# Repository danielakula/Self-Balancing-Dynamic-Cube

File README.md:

# Self-Balancing-Dynamic-Cube
Cubli inspired project for 3rd year undergraduate dissertation. Objective is to achieve balance on three edges, corner, and jump from face to edge.

# Contents
ESP32_Tests is written code for each tests done on the firmware.

Edge Balance is the code that implements an inner LQR control loop and a PI outer loop to achieve edge balance on Motor1.

UI Balance is a test which adds wireless UI onto Edge Balance.

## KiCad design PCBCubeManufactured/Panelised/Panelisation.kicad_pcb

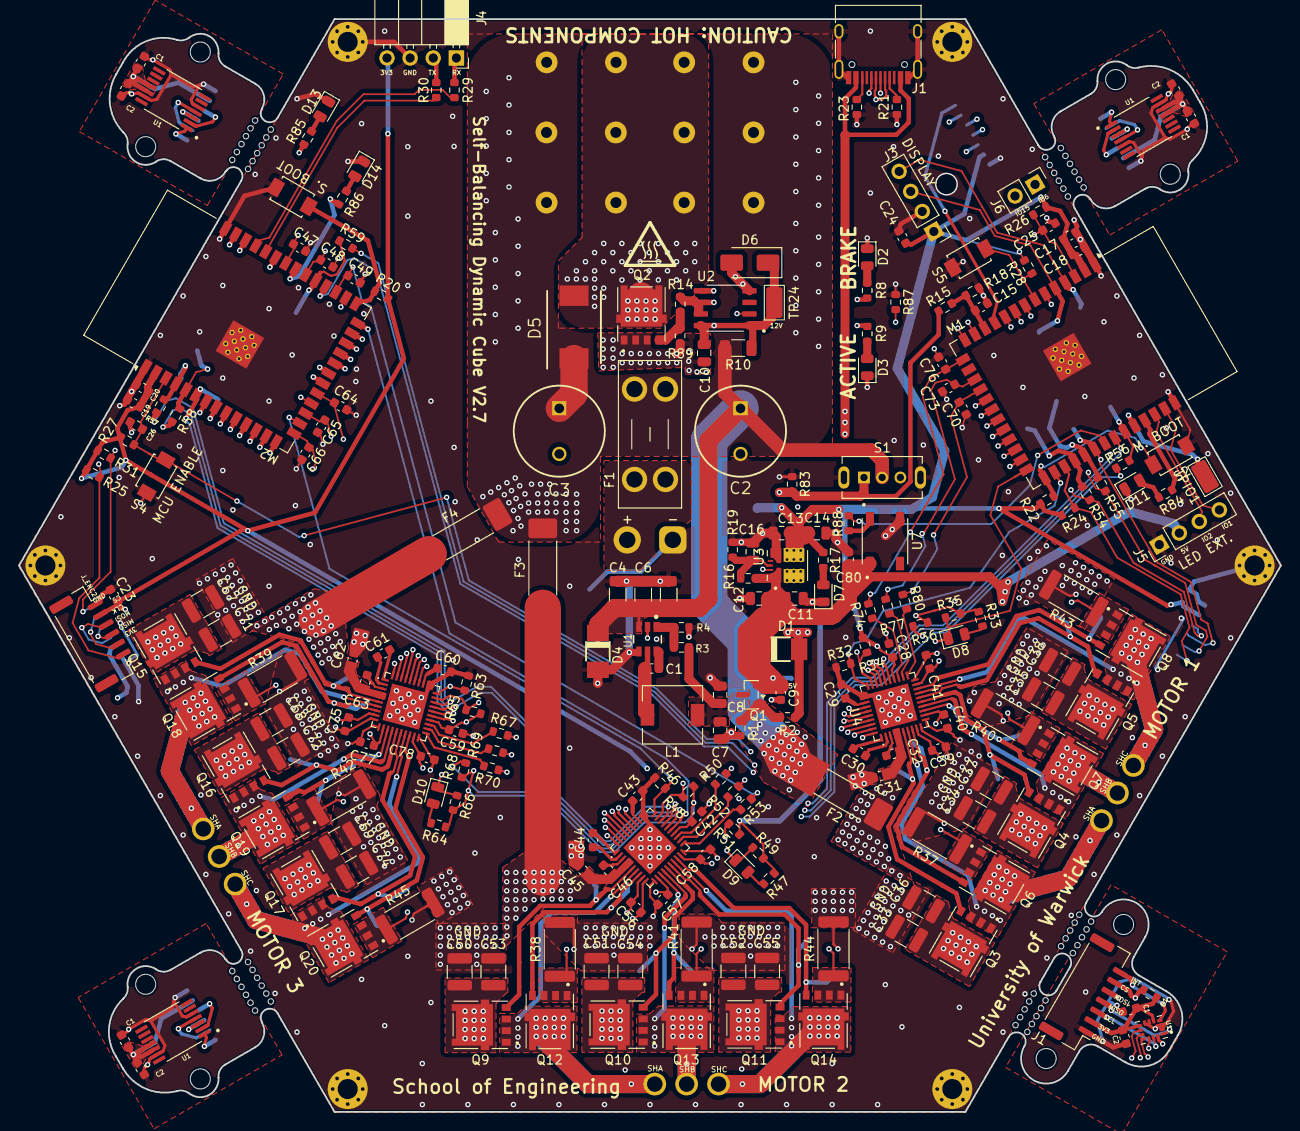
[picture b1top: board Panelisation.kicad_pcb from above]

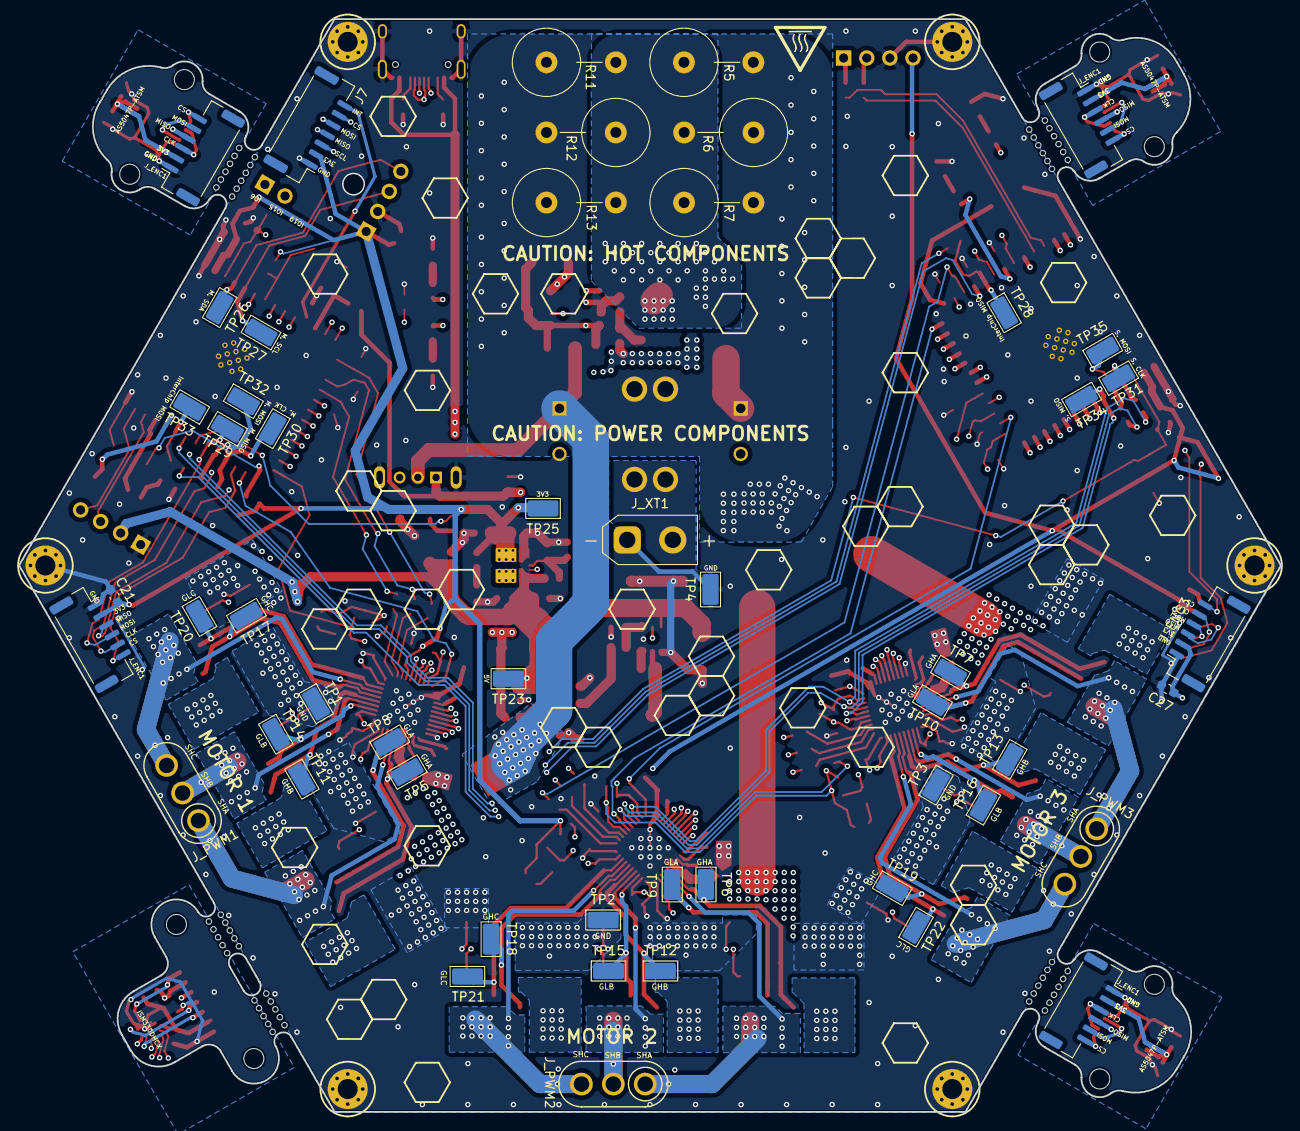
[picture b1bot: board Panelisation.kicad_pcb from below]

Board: 4 copper layers, 138.6 x 120.0 mm, 291 parts (53 on the bottom side), 181 nets.

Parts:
C1, C1#2, C1#3, C1#4, C1#5, C2#2, C15, C18, C20, C21, C23, C24, C27, C28, C31, C42, C45, C59, C62, C80: 100nF; C_0603_1608Metric
C2, C3: EEU-FC1H471L; CAPPRD500W85D1000H3200
C2#3, C2#4, C2#5, C9, C17, C19: 10uF; C_0603_1608Metric
C4, C5: 4.7uF; C_1206_3216Metric
C6: 100nF; C_1206_3216Metric
C7, C8: 47uF; C_0805_2012Metric
C10, C11, C16: 10uF; C_0805_2012Metric
C12: 100nF; C_0805_2012Metric
C13, C14: 22uF; C_0805_2012Metric
C25, C26, C29, C32, C43, C46, C60, C63: 1uF; C_0603_1608Metric
C30, C44, C61: 47nF; C_0603_1608Metric
C33, C34, C35, C36, C37, C38, C50, C51, C52, C53, C54, C55, C67, C68, C69, C71, C72, C74: 10uF; C_1210_3225Metric
C39, C40, C41, C56, C57, C58, C75, C77, C78: 1000pF; C_0603_1608Metric
C47, C48, C49, C64, C65, C66, C70, C73, C76: 2.2nF; C_0603_1608Metric
D1, D4: D_Schottky SS34; DO-214AC
D2, D8, D9, D10, D11, D14: LED R; LED_0805_2012Metric
D3, D7, D13: LED G; LED_0805_2012Metric
D5: D_Schottky SS1045; DIOM8059X256N
D6: 12V Zener; D_SMA
F1: 3568; Fuseholder_Blade_Mini_Keystone_3568
F2, F3, F4: 0456020.ER; FUSC10030X305N
H1, H2, H3, H4, H5, H6: MountingHole_Pad; MountingHole_2.19mm_M2_Pad_Via
J1, J7: Conn_01x07; JST_GH_BM07B-GHS-TBT_1x07-1MP_P1.25mm_Vertical
J1#2: USB_C_Receptacle_USB2.0_16P; USB_C_Receptacle_HRO_TYPE-C-31-M-12
J3, J5: Conn_01x04; PinHeader_1x04_P2.54mm_Vertical
J4: Conn_01x04; PinSocket_1x04_P2.54mm_Horizontal
J6: Conn_01x02; PinHeader_1x02_P2.54mm_Vertical
J_ENC1, J_ENC1#2, J_ENC1#3, J_ENC1#4, J_ENC2, J_ENC3: Conn_01x06; JST_GH_SM06B-GHS-TB_1x06-1MP_P1.25mm_Horizontal
J_PWM1, J_PWM2, J_PWM3: Conn_01x03; Amass_MR30PB-M
J_XT1: XT30UPB-M; AMASS_XT30UPB-M_1x02_P5.0mm_Vertical
L1: 4.7uH; L_6.3x6.3_H3
LOGO3, LOGO3#2: CAUTION HOT SURFACE; IEC_HotSurface_Small
M1, M2: ESP32-S3-WROOM-1
NT1, NT2, NT3, NT4, NT5, NT6, NT7, NT8, NT9, NT10: NetTie_2; NET-TIE-0.25mm
Q1: AO3401A; SOT-23
Q2, Q3, Q4, Q5, Q6, Q7, Q8, Q9, Q10, Q11, Q12, Q13, Q14, Q15, Q16, Q17, Q18, Q19, Q20: NTMFS5C612N; NTMFS5C430NT1G
R1, R1#2, R18, R19, R20, R22, R26, R27, R28, R87, R89: 10k; R_0603_1608Metric
R2: 1k; R_0603_1608Metric
R3, R15, R83: 100k; R_0603_1608Metric
R4: 19.1k; R_0603_1608Metric
R5, R6, R7, R11, R12, R13: AC07000003308JAC00; AC05
R8, R9: 2.2k; R_0603_1608Metric
R10: 330; R_1206_3216Metric
R14: 10; R_0603_1608Metric
R16: 15.8k; R_0603_1608Metric
R17: 470; R_0603_1608Metric
R21, R23: 5.1k; R_0603_1608Metric
R24, R25, R31, R32, R34, R35, R36, R46, R48, R49, R51, R63, R65, R66, R68: 10K; R_0603_1608Metric
R29, R30, R84, R85, R86, R88: 330; R_0603_1608Metric
R33, R47, R64: 1.5k; R_0603_1608Metric
R37, R38, R39, R40, R41, R42, R43, R44, R45: Shunt; R_2512_6332Metric
R50, R52, R53, R67, R69, R70, R74, R77, R80: 56; R_0603_1608Metric
R54, R55, R56, R57, R58, R59: 33; R_0603_1608Metric
S1: SS12D07VG4; SW_SS12D07VG4
S2, S3, S4, S5: TS-1088-AR02016; SW_TS-1088-AR02016
TP1, TP2, TP3, TP4, TP5, TP6, TP7, TP8, TP9, TP10, TP11, TP12, TP13, TP14, TP15, TP16, TP17, TP18, TP19, TP20, TP21, TP22, TP23, TP24, TP25, TP26, TP27, TP28, TP29, TP30, TP31, TP32, TP33, TP34, TP35: TestPoint; TestPoint_Keystone_5015_Micro_Mini
TPIO1: TestPoint; TestPoint_Keystone_5015_Micro_Mini
U1, U1#3, U1#5: AS5047P-ATSM; SOP65P640X120-14N
U1#2: LMR51625YFDDCR; DDC0006A-MFG
U1#4: ISM330DHCX; PQFN50P250X300X86-14N
U2: MCP1407-E_SN
U3: TPSM863253RDXR; VREG_TPSM863253RDXR
U4, U5, U6: DRV8323SRTAT; DRV8323SRTAT_update_solder
U7: WS2812B-B; LED_WS2812B-B

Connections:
+3V3: C1.1, C1#2.1, C1#4.1, C1#5.1, C2#2.1, C2#3.1, C2#4.1, C2#5.1, C13.2, C14.2, C17.2, C18.2, C19.2, C20.2, C21.2, C23.2, C24.2, C27.2, C28.2, C42.2, C59.2, J1.2, J3.1, J4.4, J7.2, J_ENC1.2, J_ENC1#2.2, J_ENC1#3.2, J_ENC1#4.2, J_ENC2.2, J_ENC3.2, M1.2 (3V3), M2.2 (3V3), R1#2.2, R17.2, R20.1, R22.1, R24.2, R25.2, R26.1, R27.1, R28.1, R31.2, R33.1, R34.2, R35.2, R36.2, R47.1, R48.2, R49.2, R51.2, R64.1, R65.2, R66.2, R68.2, TP25.1, U1.11 (VDD), U1.12 (VDD3V3), U1#3.11 (VDD), U1#3.12 (VDD3V3), U1#4.5 (VDD_IO), U1#4.8 (VDD), U1#5.11 (VDD), U1#5.12 (VDD3V3), U3.3 (VOUT), U3.7 (FB), U4.24 (VREF), U5.24 (VREF), U6.24 (VREF)
+5V: C9.2, C11.2, C12.2, C80.2, D1.1 (K), J5.2, Q1.2 (S), R16.1, TP23.1, U3.1 (VIN), U7.1 (VDD)
+5V Buck: C7.2, C8.2, L1.2, Q1.3 (D), R3.1
+5V USB: D1.2 (A), J1#2.A4 (VBUS), J1#2.A9 (VBUS), J1#2.B4 (VBUS), J1#2.B9 (VBUS), R2.1
/AO3401A Gate: Q1.1 (G), R1.1, R2.2
/BR3_EN: C16.2, R16.2, R19.2, U3.6 (EN)
/BR5_CB: C1#3.2, U1#2.6 (CB)
/BR5_FB: R3.2, R4.2, U1#2.1 (FB)
/BR5_SW: C1#3.1, L1.1, U1#2.5 (SW)
/BR_LEDG: D3.2 (A), R9.1
/BR_LEDR: D2.2 (A), R8.1
/CC1: J1#2.A5 (CC1), R21.2
/CC2: J1#2.B5 (CC2), R23.1
/CLK: J_ENC1.3, J_ENC1#3.3, J_ENC1#4.3, U1.2 (CLK), U1#3.2 (CLK), U1#5.2 (CLK)
/CS: J_ENC1.6, J_ENC1#3.6, J_ENC1#4.6, U1.1 (CSN), U1#3.1 (CSN), U1#5.1 (CSN)
/DIN: R88.2, U7.4 (DIN)
/Drain_Brake: D5.2 (A), Q2.5 (D), R5.1, R6.2, R7.1, R11.2, R12.1, R13.2
/Driver1/CPH1: C30.1, U4.2 (CPH)
/Driver1/CPL1: C30.2, U4.1 (CPL)
/Driver1/DVDD: C29.2, U4.33 (DVDD)
/Driver1/GHA: Q3.4 (G), TP5.1, U4.6 (GHA)
/Driver1/GHB: Q4.4 (G), TP11.1, U4.15 (GHB)
/Driver1/GHC: Q5.4 (G), TP17.1, U4.16 (GHC)
/Driver1/GLA: Q6.4 (G), TP8.1, U4.8 (GLA)
/Driver1/GLB: Q7.4 (G), TP14.1, U4.13 (GLB)
/Driver1/GLC: Q8.4 (G), TP20.1, U4.18 (GLC)
/Driver1/LED R1: D8.2 (A), R33.2
/Driver1/PhaseA: J_PWM1.1, Q3.1 (S), Q6.5 (D), U4.7 (SHA)
/Driver1/PhaseB: J_PWM1.2, Q4.1 (S), Q7.5 (D), U4.14 (SHB)
/Driver1/PhaseC: J_PWM1.3, Q5.1 (S), Q8.5 (D), U4.17 (SHC)
/Driver1/SNA: C39.1, NT4.2, U4.10 (SNA)
/Driver1/SNB: C40.1, NT2.2, U4.11 (SNB)
/Driver1/SNC: C41.1, NT3.2, U4.20 (SNC)
/Driver1/SPA: C39.2, Q6.1 (S), R37.1, U4.9 (SPA)
/Driver1/SPB: C40.2, Q7.1 (S), R40.1, U4.12 (SPB)
/Driver1/SPC: C41.2, Q8.1 (S), R43.1, U4.19 (SPC)
/Driver1/VCP1: C32.2, U4.3 (VCP)
/Driver1/VFuse: C31.2, C32.1, C33.2, C34.2, C35.2, C36.2, C37.2, C38.2, F2.1, Q3.5 (D), Q4.5 (D), Q5.5 (D), U4.4 (VM), U4.5 (VDRAIN)
/Driver2/CPH1: C44.1, U5.2 (CPH)
/Driver2/CPL1: C44.2, U5.1 (CPL)
/Driver2/DVDD: C43.2, U5.33 (DVDD)
/Driver2/GHA: Q9.4 (G), TP6.1, U5.6 (GHA)
/Driver2/GHB: Q10.4 (G), TP12.1, U5.15 (GHB)
/Driver2/GHC: Q11.4 (G), TP18.1, U5.16 (GHC)
/Driver2/GLA: Q12.4 (G), TP9.1, U5.8 (GLA)
/Driver2/GLB: Q13.4 (G), TP15.1, U5.13 (GLB)
/Driver2/GLC: Q14.4 (G), TP21.1, U5.18 (GLC)
/Driver2/LED R1: D9.2 (A), R47.2
/Driver2/PhaseA: J_PWM2.1, Q9.1 (S), Q12.5 (D), U5.7 (SHA)
/Driver2/PhaseB: J_PWM2.2, Q10.1 (S), Q13.5 (D), U5.14 (SHB)
/Driver2/PhaseC: J_PWM2.3, Q11.1 (S), Q14.5 (D), U5.17 (SHC)
/Driver2/SNA: C56.1, NT7.2, U5.10 (SNA)
/Driver2/SNB: C57.1, NT5.2, U5.11 (SNB)
/Driver2/SNC: C58.1, NT6.2, U5.20 (SNC)
/Driver2/SPA: C56.2, Q12.1 (S), R38.1, U5.9 (SPA)
/Driver2/SPB: C57.2, Q13.1 (S), R41.1, U5.12 (SPB)
/Driver2/SPC: C58.2, Q14.1 (S), R44.1, U5.19 (SPC)
/Driver2/VCP1: C46.2, U5.3 (VCP)
/Driver2/VFuse: C45.2, C46.1, C50.2, C51.2, C52.2, C53.2, C54.2, C55.2, F3.1, Q9.5 (D), Q10.5 (D), Q11.5 (D), U5.4 (VM), U5.5 (VDRAIN)
/Driver3/CPH1: C61.1, U6.2 (CPH)
/Driver3/CPL1: C61.2, U6.1 (CPL)
/Driver3/DVDD: C60.2, U6.33 (DVDD)
/Driver3/GHA: Q15.4 (G), TP7.1, U6.6 (GHA)
/Driver3/GHB: Q16.4 (G), TP13.1, U6.15 (GHB)
/Driver3/GHC: Q17.4 (G), TP19.1, U6.16 (GHC)
/Driver3/GLA: Q18.4 (G), TP10.1, U6.8 (GLA)
/Driver3/GLB: Q19.4 (G), TP16.1, U6.13 (GLB)
/Driver3/GLC: Q20.4 (G), TP22.1, U6.18 (GLC)
/Driver3/LED R1: D10.2 (A), R64.2
/Driver3/PhaseA: J_PWM3.1, Q15.1 (S), Q18.5 (D), U6.7 (SHA)
/Driver3/PhaseB: J_PWM3.2, Q16.1 (S), Q19.5 (D), U6.14 (SHB)
/Driver3/PhaseC: J_PWM3.3, Q17.1 (S), Q20.5 (D), U6.17 (SHC)
/Driver3/SNA: C75.1, NT10.2, U6.10 (SNA)
/Driver3/SNB: C77.1, NT8.2, U6.11 (SNB)
/Driver3/SNC: C78.1, NT9.2, U6.20 (SNC)
/Driver3/SPA: C75.2, Q18.1 (S), R39.1, U6.9 (SPA)
/Driver3/SPB: C77.2, Q19.1 (S), R42.1, U6.12 (SPB)
/Driver3/SPC: C78.2, Q20.1 (S), R45.1, U6.19 (SPC)
/Driver3/VCP1: C63.2, U6.3 (VCP)
/Driver3/VFuse: C62.2, C63.1, C67.2, C68.2, C69.2, C71.2, C72.2, C74.2, F4.1, Q15.5 (D), Q16.5 (D), Q17.5 (D), U6.4 (VM), U6.5 (VDRAIN)
/Gate_Brake: Q2.4 (G), R14.1, R89.1
/I.C. MISO: M2.31 (IO38), R59.1, TP28.1
/I.C. MOSI: M1.35 (IO42), R56.1, TP33.1
/LEDG: D7.2 (A), R17.1
/M. CLK: M1.30 (IO37), R54.1, TP30.1
/M. LEDR: D11.2 (A), R84.2
/M. MOSI: M1.31 (IO38), R55.1, TP32.1
/MISO: J_ENC1.4, J_ENC1#3.4, J_ENC1#4.4, U1.3 (MISO), U1#3.3 (MISO), U1#5.3 (MISO)
/MOSI: J_ENC1.5, J_ENC1#3.5, J_ENC1#4.5, U1.4 (MOSI), U1#3.4 (MOSI), U1#5.4 (MOSI)
/Out: R8.2, R14.2, U2.6 (OUT), U2.7 (OUT)
/S. CLK: M2.4 (IO4), R57.2, TP31.1
/S. LEDG: D13.2 (A), R85.2
/S. LEDR: D14.2 (A), R86.2
/S. MOSI: M2.5 (IO5), R58.2, TP35.1
/SRX: J4.1, R30.1
/STX: J4.2, R29.1
/V_XT30: F1.1, J_XT1.2 (+)
Debug1: J6.1, M1.6 (IO6)
Debug2: J6.2, M1.8 (IO15)
Display Button: M1.7 (IO7), R28.2, S5.2
Enable1: M1.28 (IO35), R32.2, U4.30 (ENABLE)
Enable2: M2.16 (IO46), R46.2, U5.30 (ENABLE)
Enable3: M2.14 (USB_D+), R63.2, U6.30 (ENABLE)
Fault1: D8.1 (K), M1.26 (IO45), R35.1, U4.25 (NFAULT)
Fault2: D9.1 (K), M2.26 (IO45), R49.1, U5.25 (NFAULT)
Fault3: D10.1 (K), M2.13 (USB_D-), R66.1, U6.25 (NFAULT)
GND: C1.2, C1#2.2, C1#4.2, C1#5.2, C2.2 (-), C2#2.2, C2#3.2, C2#4.2, C2#5.2, C3.2 (-), C4.1, C5.1, C6.1, C7.1, C8.1, C9.1, C10.2, C11.1, C12.1, C13.1, C14.1, C15.1, C16.1, C17.1, C18.1, C19.1, C20.1, C21.1, C23.1, C24.1, C25.2, C26.2, C27.1, C28.1, C29.1, C31.1, C33.1, C34.1, C35.1, C36.1, C37.1, C38.1, C42.1, C43.1, C45.1, C47.1, C48.1, C49.1, C50.1, C51.1, C52.1, C53.1, C54.1, C55.1, C59.1, C60.1, C62.1, C64.1, C65.1, C66.1, C67.1, C68.1, C69.1, C70.1, C71.1, C72.1, C73.1, C74.1, C76.1, C80.1, D2.1 (K), D3.1 (K), D4.2 (A), D6.2 (A), D7.1 (K), D11.1 (K), D13.1 (K), D14.1 (K), H1.1, H2.1, H3.1, H4.1, H5.1, H6.1, J1.1, J1#2.A1 (GND), J1#2.A12 (GND), J1#2.B1 (GND), J1#2.B12 (GND), J1#2.S1 (SHIELD), J3.2, J4.3, J5.1, J7.1, J_ENC1.1, J_ENC1#2.1, J_ENC1#3.1, J_ENC1#4.1, J_ENC2.1, J_ENC3.1, J_XT1.1 (-), M1.1 (GND), M1.40 (GND), M1.41 (GND), M2.1 (GND), M2.40 (GND), M2.41 (GND), NT2.1, NT3.1, NT4.1, NT5.1, NT6.1, NT7.1, NT8.1, NT9.1, NT10.1, Q2.1 (S), R1.2, R4.1, R18.1, R19.1, R21.1, R23.2, R32.1, R37.2, R38.2, R39.2, R40.2, R41.2, R42.2, R43.2, R44.2, R45.2, R46.1, R63.1, R83.1, R87.1, R89.2, S1.S1 (SHIELD), S1.S2 (SHIELD), S2.1, S3.1, S4.1, S5.1, TP1.1, TP2.1, TP3.1, TP4.1, U1.5 (TEST), U1.13 (GND), U1#2.4 (GND), U1#3.5 (TEST), U1#3.13 (GND), U1#4.2 (SDX), U1#4.3 (SCX), U1#4.6 (GND), U1#4.7 (GND), U1#5.5 (TEST), U1#5.13 (GND), U2.4 (GND), U2.5 (GND), U3.4 (PGND), U4.31 (CAL), U4.32 (AGND), U4.40 (PGND), U4.41 (EXP), U5.31 (CAL), U5.32 (AGND), U5.40 (PGND), U5.41 (EXP), U6.31 (CAL), U6.32 (AGND), U6.40 (PGND), U6.41 (EXP), U7.3 (VSS)
IMU_CS: J1.6, J7.6, M1.9 (IO16), R1#2.1, U1#4.12 (CS)
IMU_INT: J1.7, J7.7, M1.11 (IO18), U1#4.4 (INT1)
INHA1: M1.24 (IO47), U4.34 (INHA)
INHA2: M2.25 (IO48), U5.34 (INHA)
INHA3: M2.12 (IO8), U6.34 (INHA)
INHB1: M1.22 (IO14), U4.36 (INHB)
INHB2: M2.23 (IO21), U5.36 (INHB)
INHB3: M2.10 (IO17), U6.36 (INHB)
INHC1: M1.20 (IO12), U4.38 (INHC)
INHC2: M2.21 (IO13), U5.38 (INHC)
INHC3: M2.8 (IO15), U6.38 (INHC)
INLA1: M1.23 (IO21), U4.35 (INLA)
INLA2: M2.24 (IO47), U5.35 (INLA)
INLA3: M2.11 (IO18), U6.35 (INLA)
INLB1: M1.21 (IO13), U4.37 (INLB)
INLB2: M2.22 (IO14), U5.37 (INLB)
INLB3: M2.9 (IO16), U6.37 (INLB)
INLC1: M1.19 (IO11), U4.39 (INLC)
INLC2: M2.20 (IO12), U5.39 (INLC)
INLC3: M2.7 (IO7), U6.39 (INLC)
InterChip MISO: M1.34 (IO41), R59.2
InterChip MOSI: M2.30 (IO37), R56.2
LED1: J5.3, M1.38 (IO2)
LED2: J5.4, M1.39 (IO1)
LED3: M1.33 (IO40), R88.1
Master Boot: M1.27 (IO0), R22.2, S2.2
Master CLK: J1.3, J7.3, J_ENC1#2.3, R54.2, U1#4.13 (SCL), U4.28 (SCLK)
Master DRV1 CS: M1.25 (IO48), R34.1, U4.29 (NSCS)
Master EN: C25.1, M1.3 (EN), NT1.1, R26.2, S4.2
Master ENC1 CS: J_ENC1#2.6, M1.29 (IO36), R24.1
Master LEDR: M1.37 (TXD0), R84.1
Master MISO: J1.4, J7.4, J_ENC1#2.4, M1.32 (IO39), R36.1, TP29.1, U1#4.1 (SDO/SA0), U4.26 (SDO)
Master MOSI: J1.5, J7.5, J_ENC1#2.5, R55.2, U1#4.14 (SDA), U4.27 (SDI)
Master SCL: J3.3, M1.5 (IO5), TP27.1
Master SDA: J3.4, M1.4 (IO4), TP26.1
unnamed: R74.2, U4.23 (SOA)
unnamed: R77.2, U4.22 (SOB)
unnamed: R80.2, U4.21 (SOC)
unnamed: R50.2, U5.23 (SOA)
unnamed: R52.2, U5.22 (SOB)
unnamed: R53.2, U5.21 (SOC)
unnamed: R67.2, U6.23 (SOA)
unnamed: R69.2, U6.22 (SOB)
unnamed: R70.2, U6.21 (SOC)
SOA1: C76.2, M1.15 (IO3), R74.1
SOA2: C47.2, M2.34 (IO41), R50.1
SOA3: C64.2, M2.19 (IO11), R67.1
SOB1: C73.2, M1.17 (IO9), R77.1
SOB2: C48.2, M2.32 (IO39), R52.1
SOB3: C65.2, M2.17 (IO9), R69.1
SOC1: C70.2, M1.18 (IO10), R80.1
SOC2: C49.2, M2.29 (IO36), R53.1
SOC3: C66.2, M2.15 (IO3), R70.1
Slave Boot: M2.27 (IO0), R20.2, S3.2
Slave CLK: J_ENC2.3, J_ENC3.3, R57.1, U5.28 (SCLK), U6.28 (SCLK)
Slave DRV2 CS: M2.28 (IO35), R48.1, U5.29 (NSCS)
Slave DRV3 CS: M2.18 (IO10), R65.1, U6.29 (NSCS)
Slave EN: C26.1, M2.3 (EN), NT1.2, R27.2
Slave ENC2 CS: J_ENC2.6, M2.39 (IO1), R25.1
Slave ENC3 CS: J_ENC3.6, M2.38 (IO2), R31.1
Slave LEDG: M2.35 (IO42), R85.1
Slave LEDR: M2.33 (IO40), R86.1
Slave MISO: J_ENC2.4, J_ENC3.4, M2.6 (IO6), R51.1, R68.1, TP34.1, U5.26 (SDO), U6.26 (SDO)
Slave MOSI: J_ENC2.5, J_ENC3.5, R58.1, U5.27 (SDI), U6.27 (SDI)
Slave RX: M2.36 (RXD0), R29.2
Slave TX: M2.37 (TXD0), R30.2
TestPoint M.: M1.36 (RXD0), TPIO1.1
USB_D+: J1#2.A6 (D+), J1#2.B6 (D+), M1.14 (USB_D+)
USB_D-: J1#2.A7 (D-), J1#2.B7 (D-), M1.13 (USB_D-)
VBAT: C2.1 (+), C3.1 (+), C4.2, C5.2, C6.2, D4.1 (K), D5.1 (K), F1.2, F2.2, F3.2, F4.2, R5.2, R6.1, R7.2, R10.2, R11.1, R12.2, R13.1, S1.2, U1#2.3 (VIN)
VBat Sense: C15.2, M1.12 (IO8), R15.1, R18.2
VDD: C10.1, D6.1 (K), R9.2, R10.1, TP24.1, U2.1 (VDD), U2.8 (VDD)
VSwitch: R15.2, R83.2, S1.1, U1#2.2 (EN)
Voltage Protection: M1.10 (IO17), R87.2, U2.2 (INPUT)

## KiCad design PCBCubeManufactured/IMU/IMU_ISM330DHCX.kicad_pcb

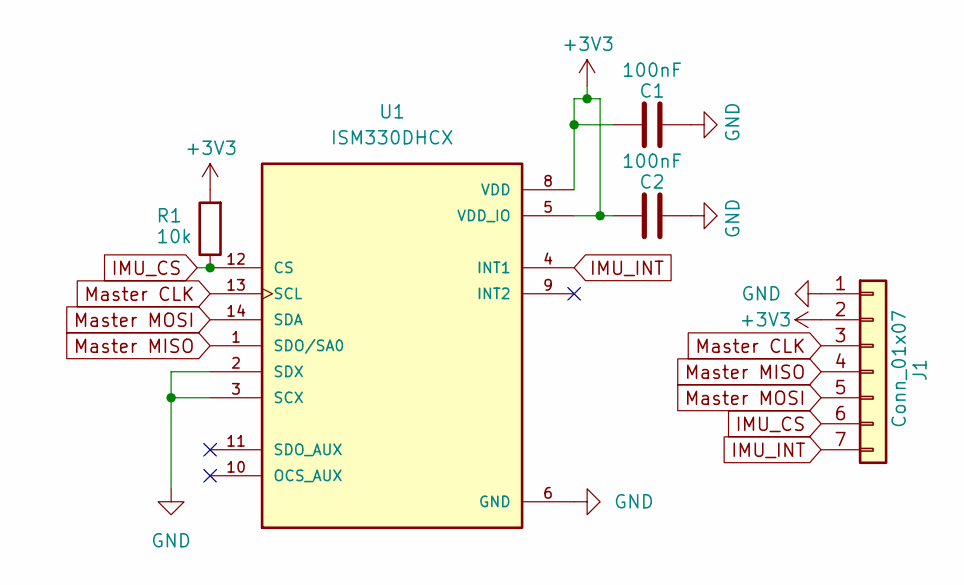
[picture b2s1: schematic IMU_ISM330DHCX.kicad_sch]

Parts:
C1, C2: 100nF; C_0603_1608Metric; LCSC C14663
J1: Conn_01x07; JST_GH_BM07B-GHS-TBT_1x07-1MP_P1.25mm_Vertical
R1: 10k; R_0603_1608Metric; LCSC C25804
U1: ISM330DHCX; PQFN50P250X300X86-14N; PARTREV 7; LCSC C2655101

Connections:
+3V3: C1.1, C2.1, J1.2, R1.2, U1.5 (VDD_IO), U1.8 (VDD)
GND: C1.2, C2.2, J1.1, U1.2 (SDX), U1.3 (SCX), U1.6 (GND), U1.7 (GND)
IMU_CS: J1.6, R1.1, U1.12 (CS)
IMU_INT: J1.7, U1.4 (INT1)
Master CLK: J1.3, U1.13 (SCL)
Master MISO: J1.4, U1.1 (SDO/SA0)
Master MOSI: J1.5, U1.14 (SDA)

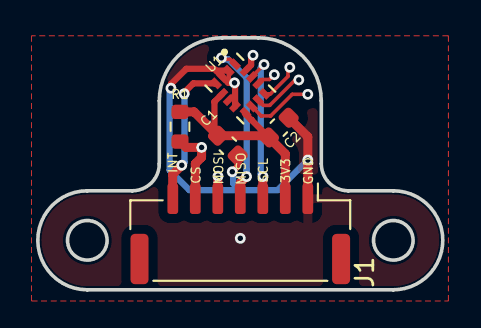
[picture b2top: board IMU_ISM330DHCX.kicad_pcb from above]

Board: 4 copper layers, 22.5 x 14.0 mm, 5 parts (0 on the bottom side), 7 nets.

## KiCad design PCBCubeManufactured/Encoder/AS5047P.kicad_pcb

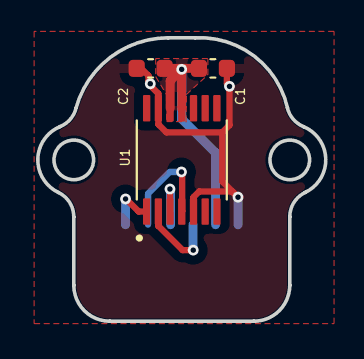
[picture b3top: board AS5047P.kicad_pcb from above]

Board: 4 copper layers, 16.0 x 15.7 mm, 4 parts (1 on the bottom side), 6 nets.

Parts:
C1: 100nF; C_0603_1608Metric
C2: 10uF; C_0603_1608Metric
J_ENC1: Conn_01x06; JST_GH_SM06B-GHS-TB_1x06-1MP_P1.25mm_Horizontal
U1: AS5047P-ATSM; SOP65P640X120-14N

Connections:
+3V3: C1.1, C2.1, J_ENC1.2, U1.11 (VDD), U1.12 (VDD3V3)
/CLK: J_ENC1.3, U1.2 (CLK)
/CS: J_ENC1.6, U1.1 (CSN)
/MISO: J_ENC1.4, U1.3 (MISO)
/MOSI: J_ENC1.5, U1.4 (MOSI)
GND: C1.2, C2.2, J_ENC1.1, U1.5 (TEST), U1.13 (GND)

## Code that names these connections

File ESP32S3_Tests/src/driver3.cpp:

#include <Arduino.h>
#include <SimpleFOC.h>
#include <SPI.h>
#include <esp_task_wdt.h>

TaskHandle_t MotorTaskHandle;
SemaphoreHandle_t spiMutex = NULL;

volatile bool pauseFOCForSPI = false;

#define SLAVE_SCK   4
#define SLAVE_MISO  6
#define SLAVE_MOSI  5

// ================================================================
//  DRIVER 3 DEFINITIONS
// ================================================================
#define ENC3_CS     41
#define DRV3_CS     10
#define DRV3_EN     20
#define nFAULT3     19

#define AH3_PIN     8
#define AL3_PIN     18
#define BH3_PIN     17
#define BL3_PIN     16
#define CH3_PIN     15
#define CL3_PIN     7

#define SOA3_PIN    11
#define SOB3_PIN    9
#define SOC3_PIN    3

#define VSENSE_PIN 8      
#define SAMPLES 64        
const float dividerRatio = 11.0; 
const float calibrationTrim = 1.008338;

#define MASTER_SDA 4
#define MASTER_SCL 5

float display_V = 0;
float display_I = 0;

// ================================================================
//  CURRENT SENSE PARAMETERS
// ================================================================
#define R_SHUNT     0.010f   // 10 mOhm
#define CSA_GAIN    20.0f    // 20 V/V
#define I_LIMIT     1.0f     // Amps

// ================================================================
//  SPI — single bus, manual CS
// ================================================================
SPIClass hwSpi(1);

// ================================================================
//  DRV8323S
// ================================================================
void drvWriteSpi(uint8_t address, uint16_t data) {
    if (xSemaphoreTake(spiMutex, pdMS_TO_TICKS(100)) == pdTRUE) {
        digitalWrite(ENC3_CS, HIGH);
        uint16_t frame = ((uint16_t)(address & 0x0F) << 11) | (data & 0x7FF);
        hwSpi.beginTransaction(SPISettings(1000000, MSBFIRST, SPI_MODE1));
        digitalWrite(DRV3_CS, LOW);
        delayMicroseconds(1);
        hwSpi.transfer16(frame);
        delayMicroseconds(1);
        digitalWrite(DRV3_CS, HIGH);
        hwSpi.endTransaction();
        xSemaphoreGive(spiMutex); 
    }
}

uint16_t drvReadSpi(uint8_t address) {
    uint16_t result = 0;
    if (xSemaphoreTake(spiMutex, portMAX_DELAY) == pdTRUE) {
        digitalWrite(ENC3_CS, HIGH);
        uint16_t frame = (1 << 15) | ((uint16_t)(address & 0x0F) << 11);
        hwSpi.beginTransaction(SPISettings(1000000, MSBFIRST, SPI_MODE1));
        digitalWrite(DRV3_CS, LOW);
        delayMicroseconds(1);
        result = hwSpi.transfer16(frame);
        delayMicroseconds(1);
        digitalWrite(DRV3_CS, HIGH);
        hwSpi.endTransaction();
        xSemaphoreGive(spiMutex);
    }
    return result & 0x7FF;
}

void initDRV8323S() {
    Serial.println("[DRV] Configuring...");
    digitalWrite(DRV3_EN, LOW);  delay(50);
    digitalWrite(DRV3_EN, HIGH); delay(100);

    drvWriteSpi(0x02, 0b00000000000);
    drvWriteSpi(0x03, 0b01100100010);
    drvWriteSpi(0x04, 0b10100100010);
    drvWriteSpi(0x05, 0b01000011001);
    drvWriteSpi(0x06, 0b01110000011);
}

// ================================================================
//  SIMPLEFOC OBJECTS
// ================================================================
BLDCDriver6PWM driver = BLDCDriver6PWM(AH3_PIN, AL3_PIN, BH3_PIN, BL3_PIN, CH3_PIN, CL3_PIN);
BLDCMotor      motor  = BLDCMotor(14, 0.5f, 195.0f, 0.00018f);
MagneticSensorSPI sensor = MagneticSensorSPI(AS5047_SPI, ENC3_CS);
LowsideCurrentSense currentSense = LowsideCurrentSense(R_SHUNT, CSA_GAIN, SOA3_PIN, SOB3_PIN, SOC3_PIN);

Commander command = Commander(Serial);
float target = 0.0f;  

bool testRunning = false;
float testTargetCurrent = 0.2f; // 1 Amp constant pull
float maxSafeSpeed = 150.0f;    // Rad/s (Adjust based on your wheel's physical limits!)

void onRunTest(char* cmd) {
    if (!testRunning) {
        target = testTargetCurrent; 
        testRunning = true;
        Serial.println("Target_I,Measured_I_q,Measured_I_d,Speed_rads"); // CSV Header
    }
}

bool kvTestRunning = false;
uint32_t testStartTime = 0;
float testVoltage = 3.0f; // 3.0V is safe and will yield ~600 RPM on a 200KV motor

void onRunKVTest(char* cmd) {
    if (!kvTestRunning) {
        // Temporarily override the controller to pure voltage mode for the test
        motor.torque_controller = TorqueControlType::voltage;
        target = testVoltage; 
        kvTestRunning = true;
        testStartTime = millis();
        Serial.println("=== STARTING KV TEST ===");
        Serial.printf("Applying %.1f Volts. Please wait 5 seconds...\n", testVoltage);
    }
}

void onTarget(char* cmd) { command.scalar(&target, cmd); }

// ================================================================
//  THE UNTHROTTLED FOC TASK (CORE 1)
// ================================================================
void motorRuntime(void * pvParameters) {
    disableCore0WDT(); 
    TaskHandle_t idleTaskHandle = xTaskGetIdleTaskHandleForCPU(0);
    if (idleTaskHandle != NULL) {
        esp_task_wdt_delete(idleTaskHandle);
    }
    vTaskPrioritySet(NULL, configMAX_PRIORITIES - 1);

    for(;;) {
        if (!pauseFOCForSPI) {
            motor.loopFOC();
            motor.move(target);
        }
    }
}

// ================================================================
//  SETUP
// ================================================================
void setup() {
    Serial.begin(115200);
    delay(3000);
    Serial.println("=== GL40 TORQUE CONTROL — 10kHz GOVERNOR ===");

    command.add('T', onTarget, "target current (A)");
    command.add('R', onRunTest, "Run Ramp Test"); 
    command.add('K', onRunKVTest, "Run True KV Test");
    spiMutex = xSemaphoreCreateMutex();

    pinMode(DRV3_CS,  OUTPUT); digitalWrite(DRV3_CS,  HIGH);
    pinMode(ENC3_CS, OUTPUT); digitalWrite(ENC3_CS, HIGH);
    pinMode(DRV3_EN,  OUTPUT); digitalWrite(DRV3_EN,  HIGH);
    pinMode(nFAULT3,  INPUT_PULLUP);

    hwSpi.begin(SLAVE_SCK, SLAVE_MISO, SLAVE_MOSI, -1);

    initDRV8323S();
    sensor.clock_speed = 20000000; 
    sensor.init(&hwSpi);

    analogReadResolution(12);
    analogSetAttenuation(ADC_11db);

    driver.pwm_frequency        = 15000;
    driver.voltage_power_supply = 15.0f;
    driver.voltage_limit        = 14.0f;
    driver.dead_zone            = 0.001f;
    driver.init();
    digitalWrite(DRV3_EN, HIGH);

    currentSense.linkDriver(&driver);
    analogRead(SOA3_PIN);  
    analogRead(SOB3_PIN);
    analogRead(SOC3_PIN);
    analogSetPinAttenuation(SOA3_PIN, ADC_11db);
    analogSetPinAttenuation(SOB3_PIN, ADC_11db);
    analogSetPinAttenuation(SOC3_PIN, ADC_11db);
    currentSense.init();

    motor.linkSensor(&sensor);
    motor.linkDriver(&driver);
    motor.linkCurrentSense(&currentSense);

    motor.torque_controller = TorqueControlType::foc_current;
    motor.controller        = MotionControlType::torque;
    motor.feed_forward_velocity = true;

    motor.PID_current_q.P           = 0.3f;
    motor.PID_current_q.I           = 50.0f;
    motor.PID_current_q.D           = 0.0f;
    motor.PID_current_q.limit       = 15.0f;
    motor.PID_current_q.output_ramp = 1000.0f;
    motor.PID_current_d.P           = 0.3f;
    motor.PID_current_d.I           = 50.0f;
    motor.PID_current_d.D           = 0.0f;
    motor.PID_current_d.limit       = 15.0f;
    motor.PID_current_d.output_ramp = 1000.0f;

    motor.LPF_current_q.Tf          = 0.01f;
    motor.LPF_current_d.Tf          = 0.01f;

    motor.voltage_sensor_align = 1.0f;
    motor.voltage_limit  = 14.0f;
    motor.current_limit  = I_LIMIT;
    motor.velocity_limit = 10.0f;

    motor.useMonitoring(Serial);
    motor.init();
    motor.initFOC();

    command.add('T', onTarget, "target current (A)");
    
    xTaskCreatePinnedToCore(
        motorRuntime,
        "MotorTask",
        10000,
        NULL,
        5,                  
        &MotorTaskHandle,
        0);          
}

// ================================================================
//  LOOP (CORE 0)
// ================================================================
void loop() {
    command.run();
    bool ledState = LOW;

    static uint32_t last = 0;
    if (millis() - last > 500) {

        // 2. Get DQ currents
        DQCurrent_s foc = currentSense.getFOCCurrents(motor.electrical_angle);
        float totalCurrent = hypot(foc.q, foc.d);

        // 3. Serial Logging
        Serial.printf("Iq: %.2fA | Id: %.2fA | Target: %.2fA | Vel: %.1f\n",
             foc.q, foc.d, target, motor.shaft_velocity);

        // 4. THE FIX: Only talk to the DRV8323 if the hardware fault pin triggers
        if (digitalRead(nFAULT3) == LOW) {
            // Now, Core 1 only steals the SPI bus if there is a literal emergency
            uint16_t f1 = drvReadSpi(0x00);
            uint16_t f2 = drvReadSpi(0x01);
            Serial.printf(">>> [DRV FAULT] 0x%03X : 0x%03X <<<\n", f1, f2);
        }

        last = millis();
    }
}

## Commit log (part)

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2026-04-09 Update README with project details and test descriptions
    Added descriptions for ESP32_Tests, Edge Balance, and Motor Control sections.
2026-04-29 Create MATLAB
2026-04-29 Add MATLAB directory
